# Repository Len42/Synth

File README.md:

# Synth

## Designs for my Eurorack synthesizer modules

This repo is where I am sharing my modular synthesizer designs.

[See here](https://lenp.net/synth/) for more info.

Please note that I am a hobbyist, not a trained electronics engineer! These designs are not perfect. The modules work for me, but I can't promise they'll work for everyone who builds them.

These designs are shared as open source. See the license details in each project and source file.

-- Len

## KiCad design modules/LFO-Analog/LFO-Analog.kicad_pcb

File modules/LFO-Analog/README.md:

# Dual Analog LFO

## 4HP Eurorack Module

### Features
- Two independent analog LFOs
- LFO rate from approximately 0.01 Hz (100 seconds) to 170 Hz, in two ranges
- Each LFO has sine and square wave outputs
- Not voltage controlled. Use your fingers! 👌

### Notes
(I have also made a [voltage-controlled digital LFO](https://github.com/Len42/Synth/tree/main/modules/LFO-DigiVC#readme).)

PCB layouts are provided in KiCad and gerber formats. A PCB layout for a drilled front panel (with no labels) is also included.

The PCBs that I used can be ordered from OSH Park. The designs are here:
- [Front panel](https://oshpark.com/shared_projects/gXxsPQ2r)
- [Controls board](https://oshpark.com/shared_projects/Vs8kgjxu)
- [Main board](https://oshpark.com/shared_projects/36ruR2I4)

There is a [parts list](bom.csv) in spreadsheet-friendly text format.

Please note that I am a hobbyist, not a trained electronics engineer. No guarantees!

### Software Used

* [KiCad](https://www.kicad.org/) 8.0.2

<hr /><div><div style="float:left; padding-right:10px;"></div><div style="xfloat:left; padding-left:10px;"><br />© 2024 Len Popp CC BY<br />This work is licensed under a <a rel="license" href="http://creativecommons.org/licenses/by/4.0/">Creative Commons Attribution 4.0 International License</a>.</div></div>

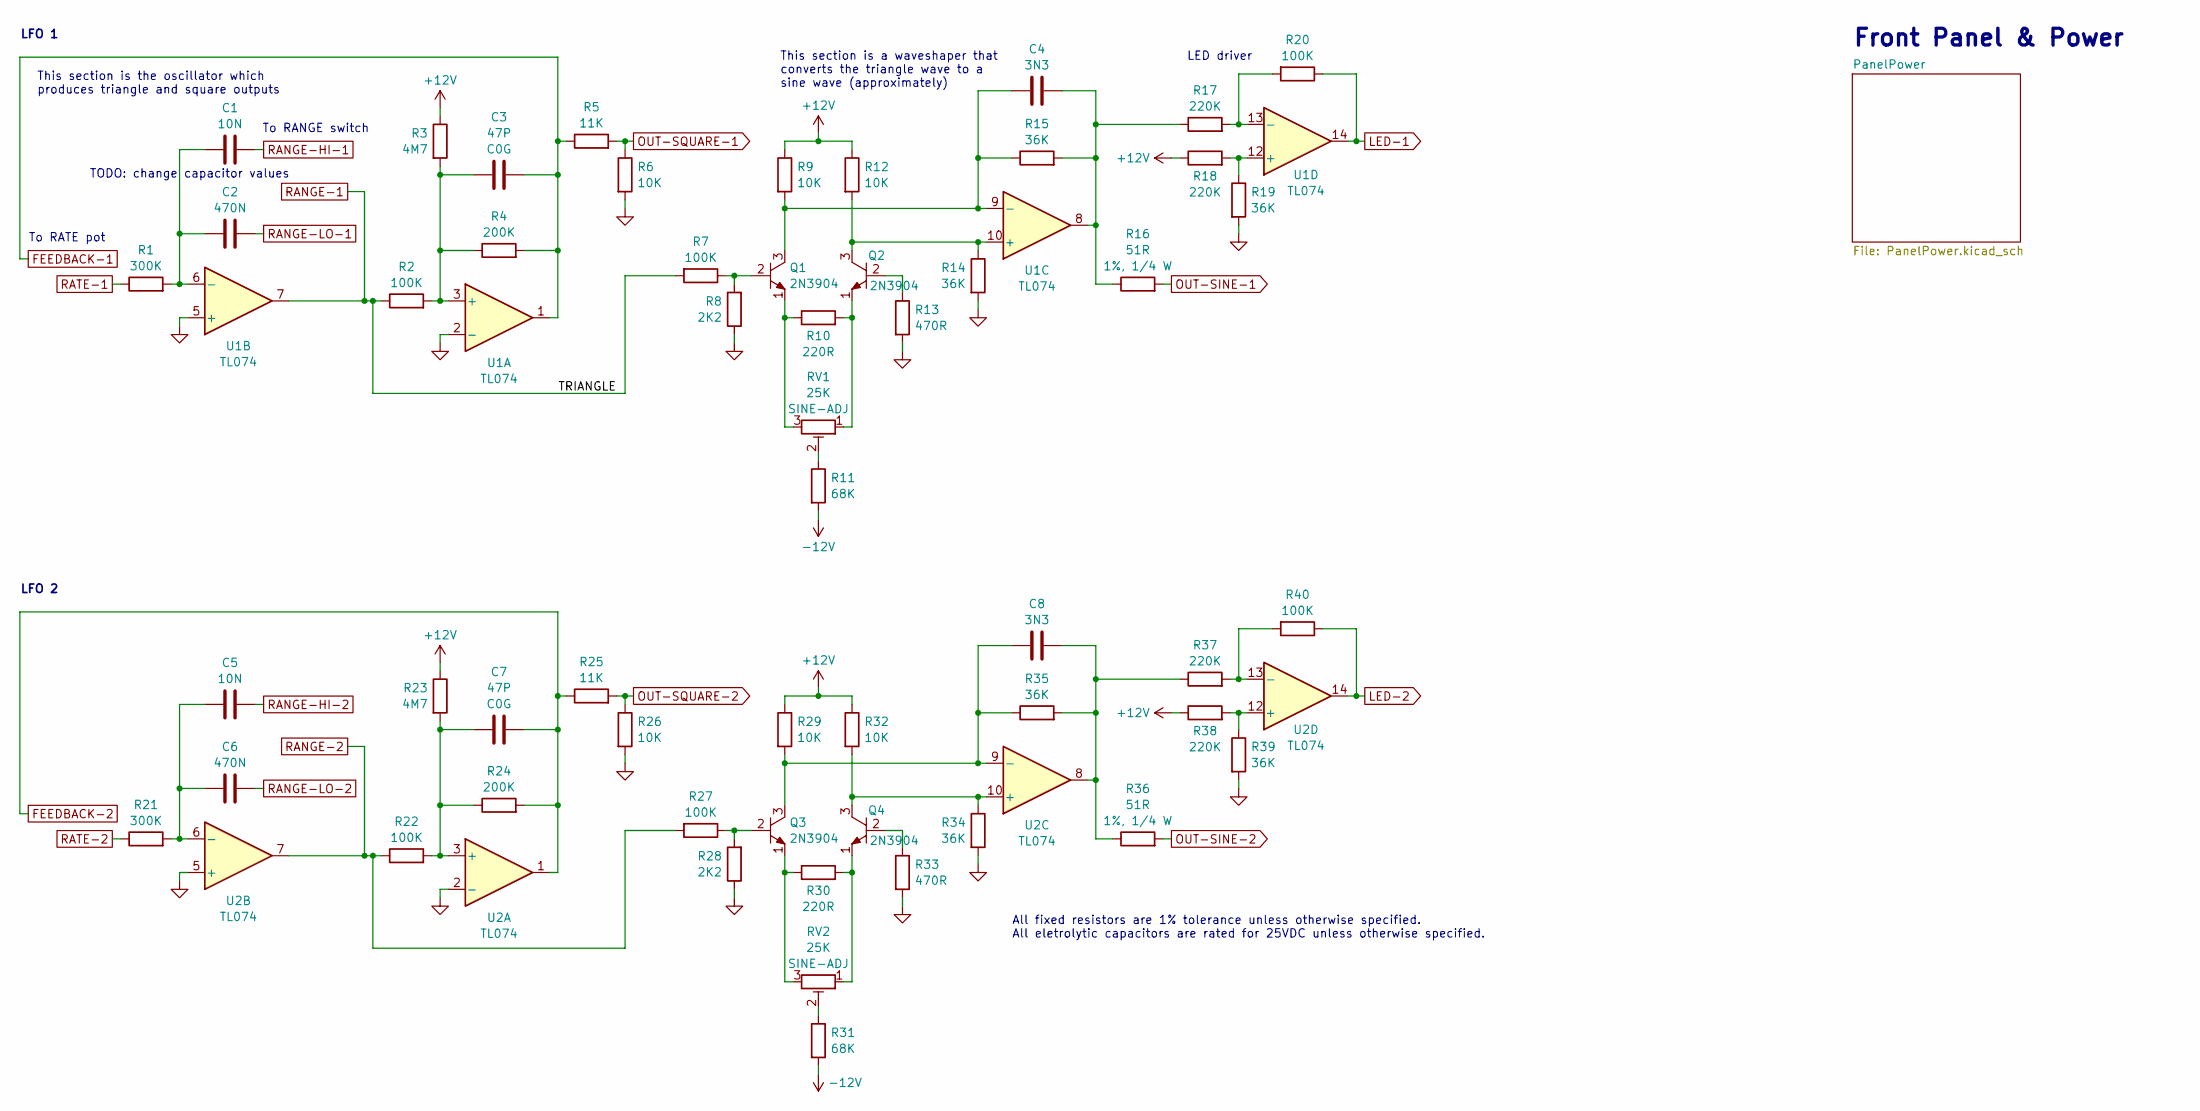
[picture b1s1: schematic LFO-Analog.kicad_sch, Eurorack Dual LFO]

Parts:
C1, C5: 10N; C_Rect_Kemet_L7.2mm_W2.5mm_P5mm; ManufacturerPartNum R82EC2100SH50J
C2, C6: 470N; C_Rect_L7.2mm_W4.5mm_P5.00mm; ManufacturerPartNum R82DC3470SH60J
C3, C7: 47P; C_Disc_D5.0mm_W2.5mm_P2.50mm; ManufacturerPartNum K470J15C0GF53L2
C4, C8: 3N3; C_Rect_Kemet_L7.2mm_W2.5mm_P5mm; ManufacturerPartNum R82EC1330AA50K
Q1, Q2, Q3, Q4: 2N3904; TO-92_Inline_Wide; ManufacturerPartNum 2N3904 PBFREE
R1, R21: 300K; R_Axial_DIN0207_L6.3mm_D2.5mm_P7.62mm_Horizontal; ManufacturerPartNum MFR-12FTF52-300K
R2, R7, R20, R22, R27, R40: 100K; R_Axial_DIN0207_L6.3mm_D2.5mm_P7.62mm_Horizontal; ManufacturerPartNum MFR-12FTF52-100K
R3, R23: 4M7; R_Axial_DIN0207_L6.3mm_D2.5mm_P7.62mm_Horizontal; ManufacturerPartNum MFR-12FTF52-4M7
R4, R24: 200K; R_Axial_DIN0207_L6.3mm_D2.5mm_P7.62mm_Horizontal; ManufacturerPartNum MFR-12FTF52-200K
R5, R25: 11K; R_Axial_DIN0207_L6.3mm_D2.5mm_P7.62mm_Horizontal; ManufacturerPartNum MFR-12FTF52-11K
R6, R9, R12, R26, R29, R32: 10K; R_Axial_DIN0207_L6.3mm_D2.5mm_P7.62mm_Horizontal; ManufacturerPartNum MFR-12FTF52-10K
R8, R28: 2K2; R_Axial_DIN0207_L6.3mm_D2.5mm_P7.62mm_Horizontal; ManufacturerPartNum MFR-12FTF52-2K2
R10, R30: 220R; R_Axial_DIN0207_L6.3mm_D2.5mm_P7.62mm_Horizontal; ManufacturerPartNum MFR-12FTF52-220R
R11, R31: 68K; R_Axial_DIN0207_L6.3mm_D2.5mm_P7.62mm_Horizontal; ManufacturerPartNum MFR-12FTF52-68K
R13, R33: 470R; R_Axial_DIN0207_L6.3mm_D2.5mm_P7.62mm_Horizontal; ManufacturerPartNum MFR-12FTF52-470R
R14, R15, R19, R34, R35, R39: 36K; R_Axial_DIN0207_L6.3mm_D2.5mm_P7.62mm_Horizontal; ManufacturerPartNum MFR-12FTF52-36K
R16, R36: 51R; R_Axial_DIN0207_L6.3mm_D2.5mm_P10.16mm_Horizontal; ManufacturerPartNum MFR-25FBF52-51R
R17, R18, R37, R38: 220K; R_Axial_DIN0207_L6.3mm_D2.5mm_P7.62mm_Horizontal; ManufacturerPartNum MFR-12FTF52-220K
RV1, RV2: 25K; Potentiometer_Bourns_3296W_Vertical; ManufacturerPartNum PV36W253C01B00
U1, U2: TL074; DIP-14_W7.62mm; ManufacturerPartNum TL074BCN

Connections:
+12V: R3.1, R9.1, R12.1, R18.1, R23.1, R29.1, R32.1, R38.1; also elsewhere on the board
-12V: R11.2, R31.2; also elsewhere on the board
FEEDBACK-1: C3.2, R4.2, R5.1, U1.1; also elsewhere on the board
FEEDBACK-2: C7.2, R24.2, R25.1, U2.1; also elsewhere on the board
GND: R6.2, R8.1, R13.2, R14.2, R19.2, R26.2, R28.1, R33.2, R34.2, R39.2, U1.2 (-), U1.5 (+), U2.2 (-), U2.5 (+); also elsewhere on the board
LED-1: R20.1, U1.14; also elsewhere on the board
LED-2: R40.1, U2.14; also elsewhere on the board
unnamed: C4.2, R15.2, R16.1, R17.1, U1.8
unnamed: C8.2, R35.2, R36.1, R37.1, U2.8
unnamed: Q1.2 (B), R7.1, R8.2
unnamed: C4.1, Q1.3 (C), R9.2, R15.1, U1.9 (-)
unnamed: Q1.1 (E), R10.1, RV1.3
unnamed: Q2.2 (B), R13.1
unnamed: Q2.3 (C), R12.2, R14.1, U1.10 (+)
unnamed: Q2.1 (E), R10.2, RV1.1
unnamed: Q3.2 (B), R27.1, R28.2
unnamed: C8.1, Q3.3 (C), R29.2, R35.1, U2.9 (-)
unnamed: Q3.1 (E), R30.1, RV2.3
unnamed: Q4.2 (B), R33.1
unnamed: Q4.3 (C), R32.2, R34.1, U2.10 (+)
unnamed: Q4.1 (E), R30.2, RV2.1
unnamed: R11.1, RV1.2
unnamed: R31.1, RV2.2
unnamed: C3.1, R2.2, R3.2, R4.1, U1.3 (+)
unnamed: C1.1, C2.1, R1.2, U1.6 (-)
unnamed: R18.2, R19.1, U1.12 (+)
unnamed: R17.2, R20.2, U1.13 (-)
unnamed: C7.1, R22.2, R23.2, R24.1, U2.3 (+)
unnamed: C5.1, C6.1, R21.2, U2.6 (-)
unnamed: R38.2, R39.1, U2.12 (+)
unnamed: R37.2, R40.2, U2.13 (-)
OUT-SINE-1: R16.2; also elsewhere on the board
OUT-SINE-2: R36.2; also elsewhere on the board
OUT-SQUARE-1: R5.2, R6.1; also elsewhere on the board
OUT-SQUARE-2: R25.2, R26.1; also elsewhere on the board
RANGE-1: R2.1, R7.2, U1.7; also elsewhere on the board
RANGE-2: R22.1, R27.2, U2.7; also elsewhere on the board
RANGE-HI-1: C1.2; also elsewhere on the board
RANGE-HI-2: C5.2; also elsewhere on the board
RANGE-LO-1: C2.2; also elsewhere on the board
RANGE-LO-2: C6.2; also elsewhere on the board
RATE-1: R1.1; also elsewhere on the board
RATE-2: R21.1; also elsewhere on the board

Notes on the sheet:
LFO 2
All fixed resistors are 1% tolerance unless otherwise specified. All eletrolytic capacitors are rated for 25VDC unless otherwise specified.
LED driver
TODO: change capacitor values
To RANGE switch
This section is the oscillator which produces triangle and square outputs
Front Panel & Power
LFO 1
This section is a waveshaper that converts the triangle wave to a sine wave (approximately)
To RATE pot

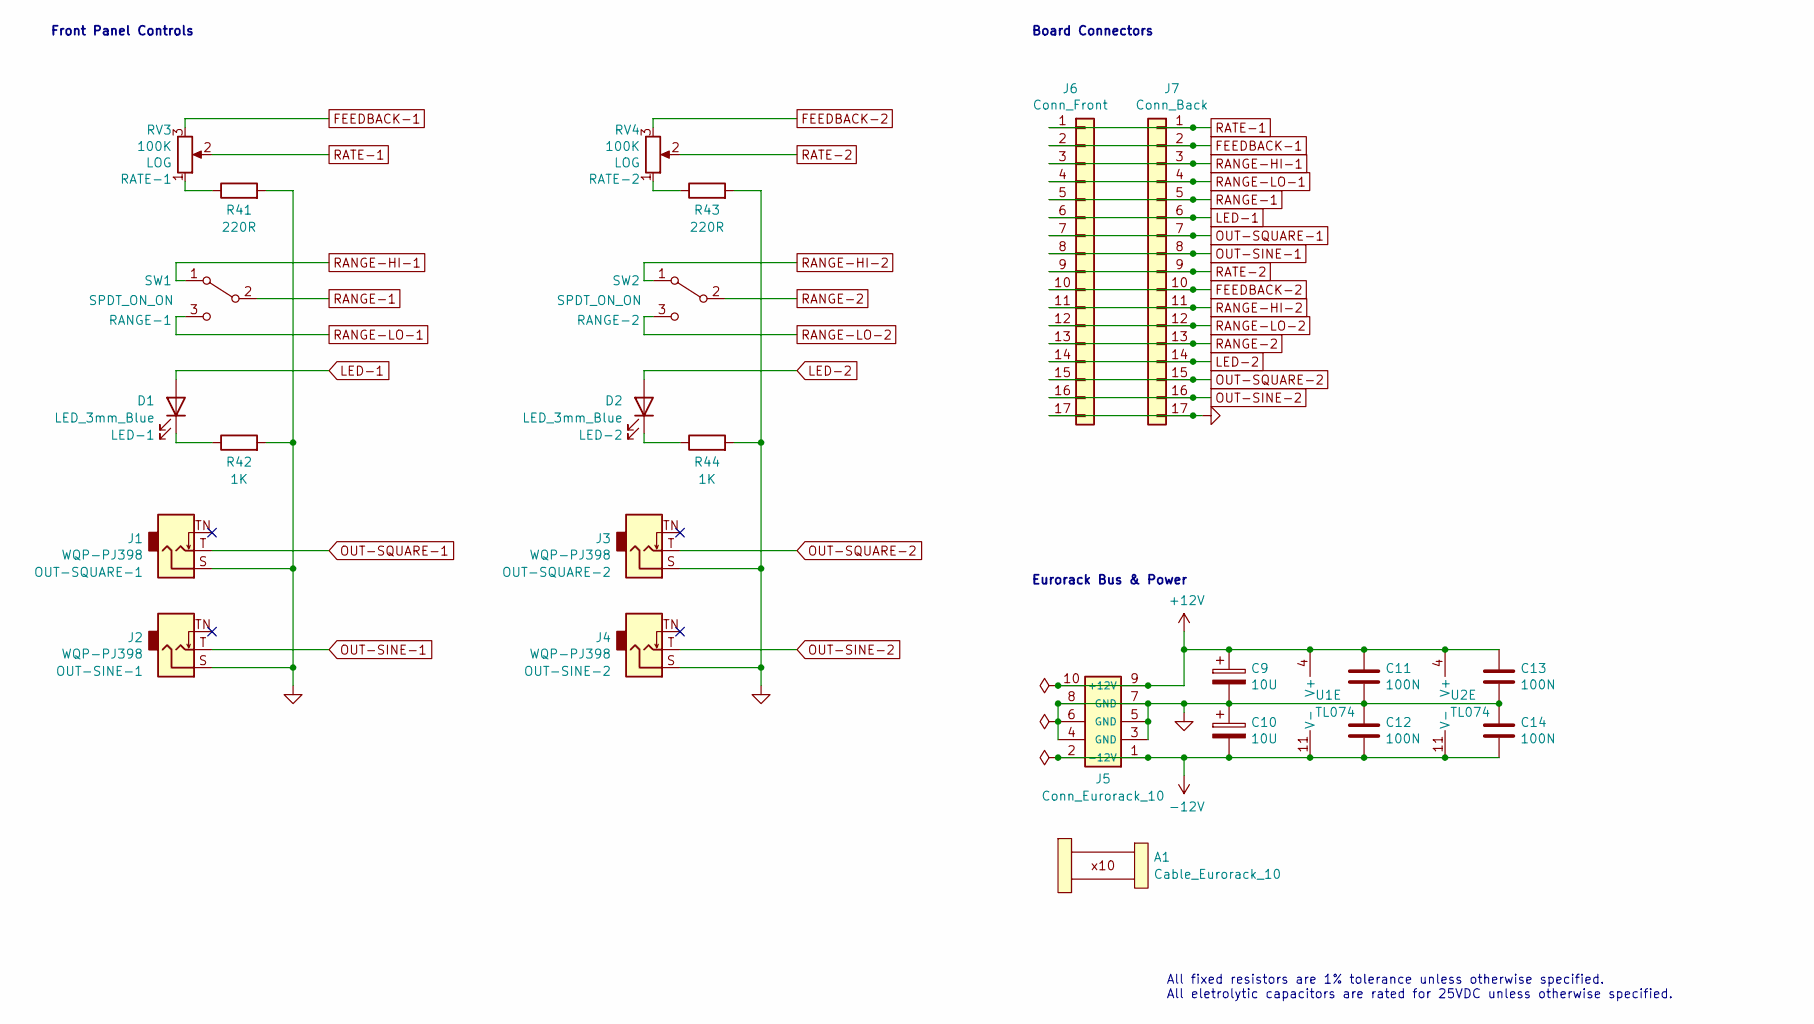
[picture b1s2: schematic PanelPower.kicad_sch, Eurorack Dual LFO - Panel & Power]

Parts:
A1: Cable_Eurorack_10; NoFootprint
C9, C10: 10U; CP_Radial_D5.0mm_P2.50mm; ManufacturerPartNum ECE-A1VKS100I
C11, C12, C13, C14: 100N; C_Disc_D5.0mm_W2.5mm_P2.50mm; ManufacturerPartNum FG18X7R1H104KNT06
D1, D2: LED_3mm_Blue; LED_D3.0mm_Clear; ManufacturerPartNum WP710A10QBD/D
J1, J2, J3, J4: WQP-PJ398; Jack_3.5mm_QingPu_WQP-PJ398SM_Vertical; ManufacturerPartNum PJ398SM / WQP518MA
J5: Conn_Eurorack_10; IDC-Header-Eurorack-10-TH; ManufacturerPartNum 61201021621
J6: Conn_Front; PinSocket_1x17_P2.54mm_Vertical
J7: Conn_Back; PinHeader_1x17_P2.54mm_Horizontal
R41, R43: 220R; R_Axial_DIN0207_L6.3mm_D2.5mm_P7.62mm_Horizontal; ManufacturerPartNum MFR-12FTF52-220R
R42, R44: 1K; R_Axial_DIN0207_L6.3mm_D2.5mm_P7.62mm_Horizontal; ManufacturerPartNum MFR-12FTF52-1K
RV3, RV4: 100K; Potentiometer_Alpha_RD901F-40-00D_Single_Vertical; ManufacturerPartNum RD901F-*
SW1, SW2: SPDT_ON_ON; SW_SPDT_THT_2.54; ManufacturerPartNum 10TC410
U1, U2: TL074; DIP-14_W7.62mm; ManufacturerPartNum TL074BCN

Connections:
+12V: C9.1, C11.1, C13.1, J5.9 (+12V), J5.10, U1.4 (V+), U2.4 (V+); also elsewhere on the board
-12V: C10.2, C12.2, C14.2, J5.1 (-12V), J5.2, U1.11 (V-), U2.11 (V-); also elsewhere on the board
FEEDBACK-1: J6.2, J7.2, RV3.3; also elsewhere on the board
FEEDBACK-2: J6.10, J7.10, RV4.3; also elsewhere on the board
GND: C9.2, C10.1, C11.2, C12.1, C13.2, C14.1, J1.S, J2.S, J3.S, J4.S, J5.3 (GND), J5.4, J5.5 (GND), J5.6, J5.7 (GND), J5.8, J6.17, J7.17, R41.2, R42.2, R43.2, R44.2; also elsewhere on the board
LED-1: D1.2 (A), J6.6, J7.6; also elsewhere on the board
LED-2: D2.2 (A), J6.14, J7.14; also elsewhere on the board
unnamed: D1.1 (K), R42.1
unnamed: D2.1 (K), R44.1
unnamed: R41.1, RV3.1
unnamed: R43.1, RV4.1
OUT-SINE-1: J2.T, J6.8, J7.8; also elsewhere on the board
OUT-SINE-2: J4.T, J6.16, J7.16; also elsewhere on the board
OUT-SQUARE-1: J1.T, J6.7, J7.7; also elsewhere on the board
OUT-SQUARE-2: J3.T, J6.15, J7.15; also elsewhere on the board
RANGE-1: J6.5, J7.5, SW1.2 (B); also elsewhere on the board
RANGE-2: J6.13, J7.13, SW2.2 (B); also elsewhere on the board
RANGE-HI-1: J6.3, J7.3, SW1.1 (A); also elsewhere on the board
RANGE-HI-2: J6.11, J7.11, SW2.1 (A); also elsewhere on the board
RANGE-LO-1: J6.4, J7.4, SW1.3 (C); also elsewhere on the board
RANGE-LO-2: J6.12, J7.12, SW2.3 (C); also elsewhere on the board
RATE-1: J6.1, J7.1, RV3.2; also elsewhere on the board
RATE-2: J6.9, J7.9, RV4.2; also elsewhere on the board

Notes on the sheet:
All fixed resistors are 1% tolerance unless otherwise specified. All eletrolytic capacitors are rated for 25VDC unless otherwise specified.
Eurorack Bus & Power
Board Connectors
Front Panel Controls

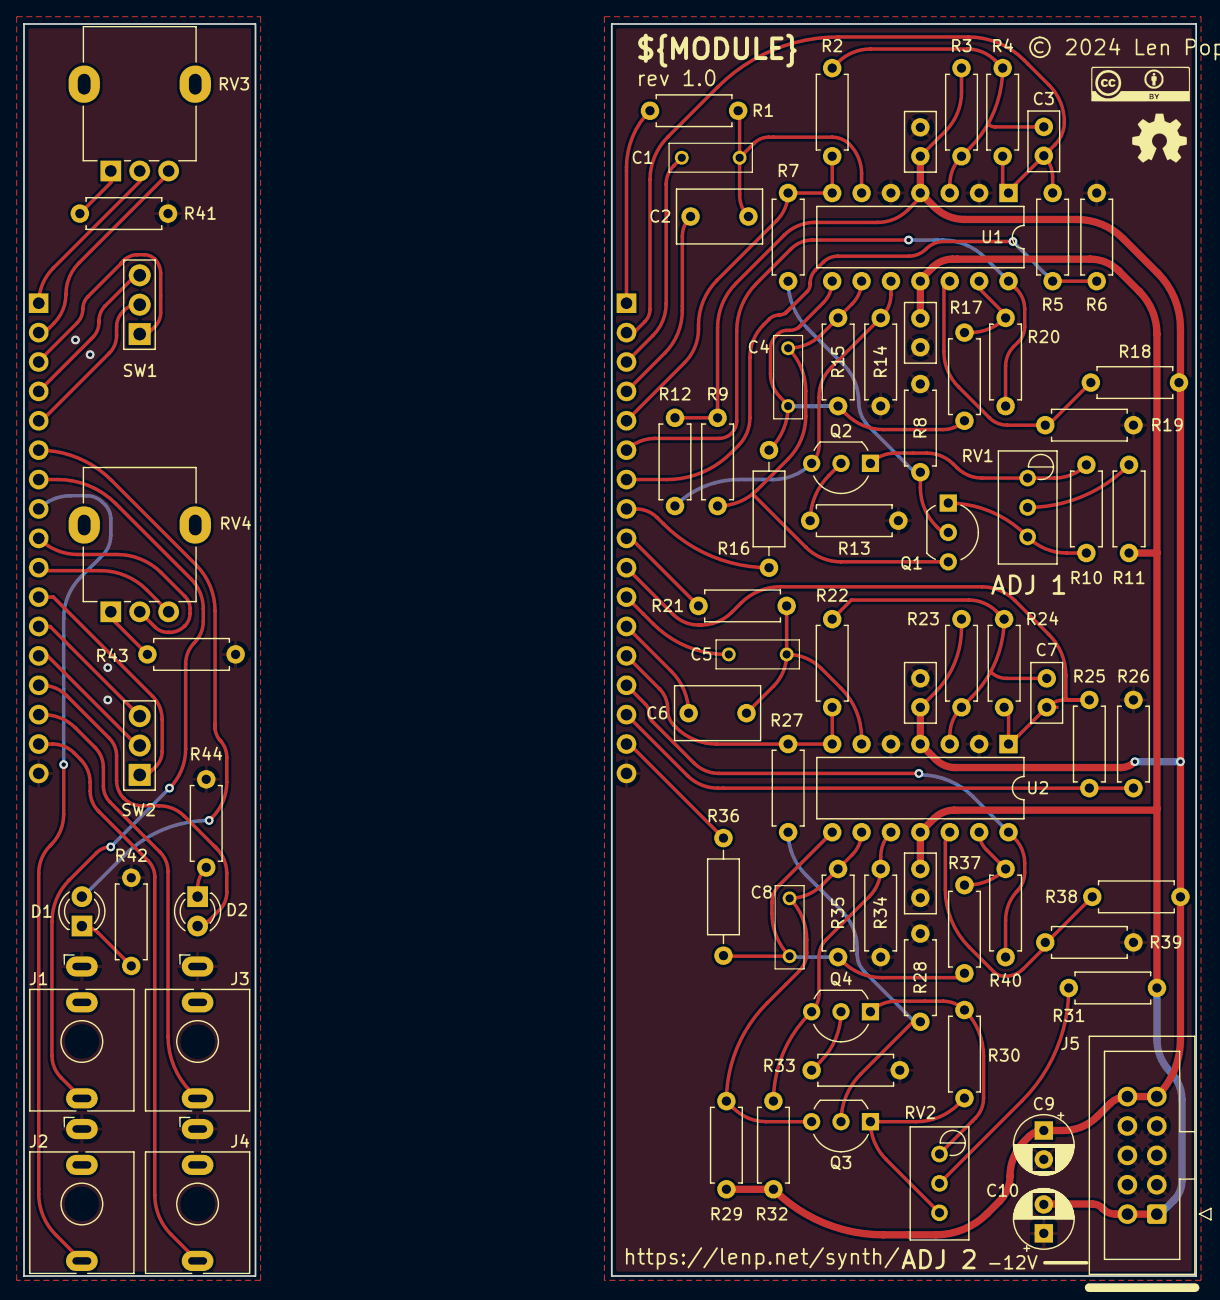
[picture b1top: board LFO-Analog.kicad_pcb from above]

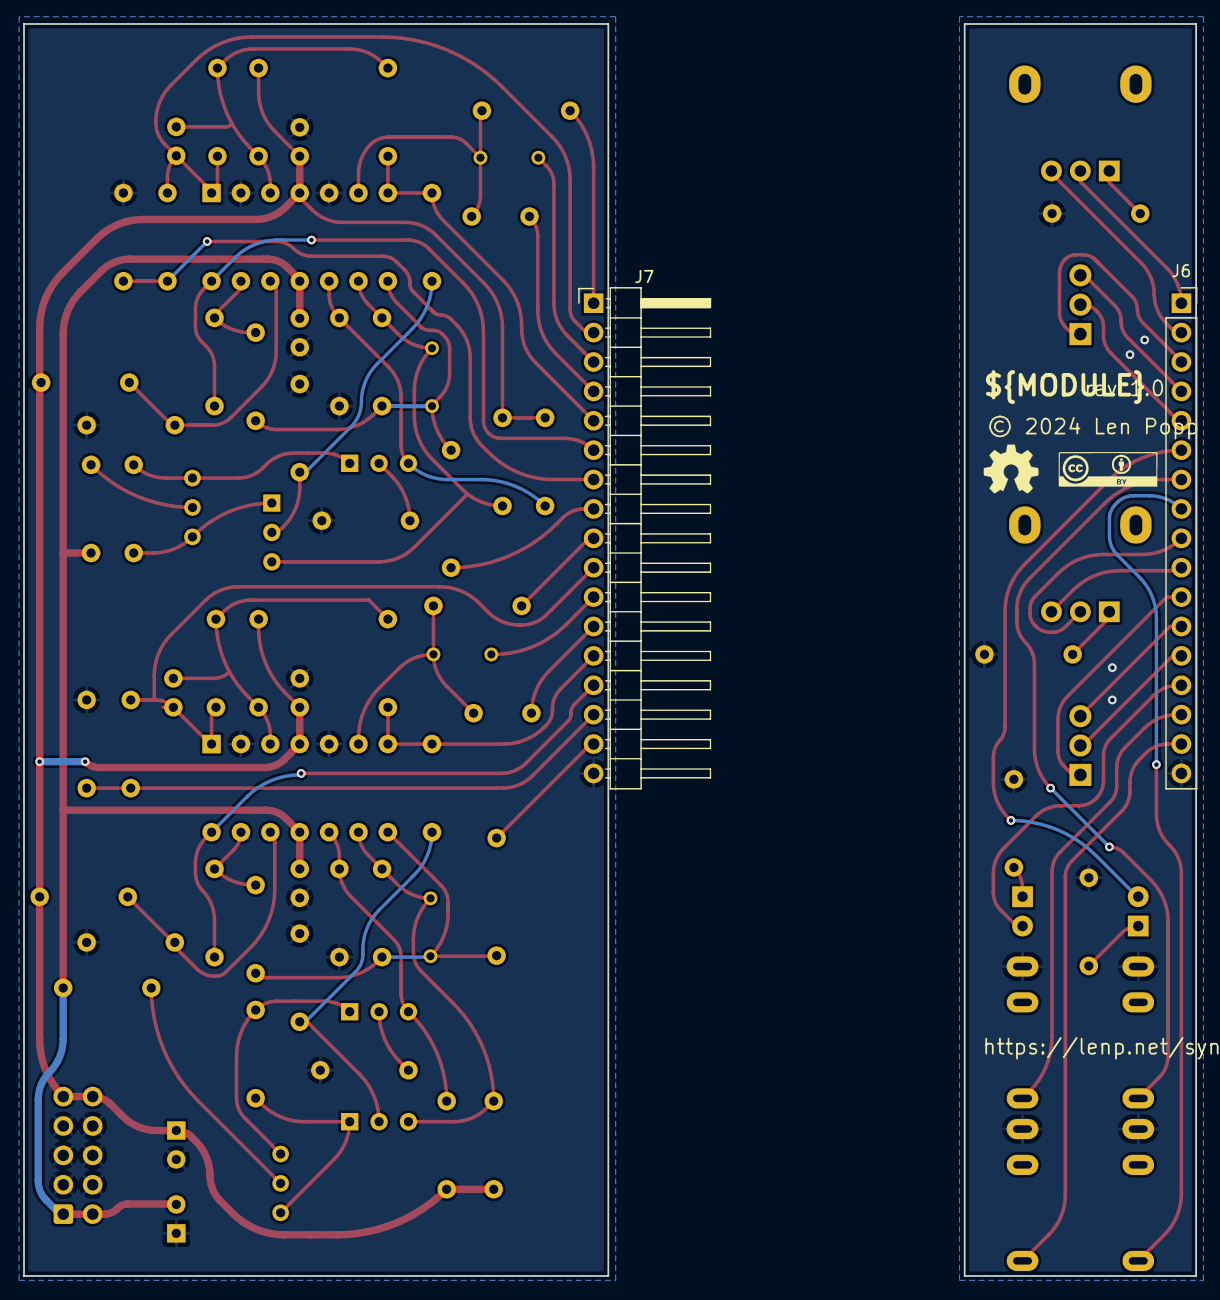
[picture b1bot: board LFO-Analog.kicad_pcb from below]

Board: 2 copper layers, 101.3 x 108.2 mm, 83 parts (4 on the bottom side), 47 nets.

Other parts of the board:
G1, G2: Logo_CC_BY
G3, G4: Logo_OSHW

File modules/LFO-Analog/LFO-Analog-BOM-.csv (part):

Ref,Qty,Value,Value2,Note,Description,Datasheet,Manufacturer,ManuPartNum,Distributor1,DistributorPartNum1,DistributorPartLink1,Distributor2,DistributorPartNum2,DistributorPartLink2,Distributor3,DistributorPartNum3,DistributorPartLink3
"A1","1","Cable_Eurorack_10","","Length as required","Eurorack 16-10 pin power cable","","","","Thonk","","https://www.thonk.co.uk/shop/eurorack-power-cables/","SynthCube","","https://synthcube.com/cart/eurorack-ribbon-power-cables","Modular Addict","","https://modularaddict.com/parts/eurorack-power-cables-1"
"C1 C5","2","3N3","","PPS for best results","Capacitor - Film","","","","","","","","","","","",""
"C2 C6","2","680N","","PPS for best results","Capacitor - Film","","","","","","","","","","","",""
"C3 C7","2","47P","C0G","","Capacitor - Ceramic","","","","","","","","","","","",""
"C4 C8","2","3N3","","","Capacitor - Film","","","","","","","","","","","",""
"C9 C10","2","10U","35 VDC","12 V decoupling","Capacitor - Electrolytic - 12 V decoupling","https://www.mouser.ca/datasheet/2/315/ABA0000C1059-947582.pdf","Panasonic","ECE-A1VKS100I","Mouser","667-ECE-A1VKS100I","https://www.mouser.ca/ProductDetail/667-ECE-A1VKS100I","Thonk","Group_Eurorack_DIY_Essential","https://www.thonk.co.uk/shop/eurorack-diy-essentials/","","",""
"C11 C12 C13 C14","4","100N","","IC decoupling","Capacitor - Ceramic - IC decoupling","https://product.tdk.com/system/files/dam/doc/product/capacit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","TDK","FG18X7R1H104KNT06","Mouser","810-FG18X7R1H104KNT6","https://www.mouser.ca/ProductDetail/810-FG18X7R1H104KNT6","","","","","",""
"D1 D2","2","LED_3mm_Blue","","","Blue Light Emitting Diode","https://www.mouser.ca/datasheet/2/239/Lite-On_LTL17KTBS3KS-0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","Kingbright","WP710A10QBD/D","Mouser","604-WP710A10QBD/D","https://www.mouser.ca/ProductDetail/Kingbright/WP710A10QBD-D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","","","","","",""
"J1 J2 J3 J4","4","WQP-PJ398","","","Audio Jack, 2 Poles (Mono / TS), Switched T Pole (Normalling), QingPu / Thonkiconn","http://www.qingpu-electronics.com/en/products/WQP-PJ398SM-362.html","QingPu / Thonk","PJ398SM / WQP518MA","Thonk","PJ398SM","https://www.thonk.co.uk/shop/thonkiconn/","SynthCube","WQP518MA","https://synthcube.com/cart/3-5mm-euro-jacks","Adafruit","4031","https://www.adafruit.com/product/4031"
"J5","1","Conn_Eurorack_10","","","Eurorack 10-pin board power connector","https://www.mouser.ca/datasheet/2/445/61201021621-1717731.pdf","Wurth Elektronik","61201021621","Mouser","710-61201021621","https://www.mouser.ca/ProductDetail/Wurth-Elektronik/6120102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","Thonk","","https://www.thonk.co.uk/shop/eurorack-diy-essentials/","","",""
"J6","1","Conn_Front","","","Generic connector, single row, 01x17, script generated (kicad-library-utils/schlib/autogen/connector/)","","","","Adafruit","598","https://www.adafruit.com/product/598","Mouser","710-61303211821","https://www.mouser.ca/ProductDetail/Wurth-Elektronik/6130321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","","",""
"J7","1","Conn_Back","","","Generic connector, single row, 01x17, script generated (kicad-library-utils/schlib/autogen/connector/)","","","","Adafruit","1540","https://www.adafruit.com/product/1540","Mouser","649-1012937993601BLF","https://www.mouser.ca/ProductDetail/Amphenol-FCI/10129379-93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","","",""
"Q1 Q2 Q3 Q4","4","2N3904","","","Small Signal NPN Transistor, 0.2A Ic, 40V Vce, TO-92","https://www.onsemi.com/pub/Collateral/2N3903-D.PDF","Central Semiconductor","2N3904 PBFREE","Mouser","610-2N3904","https://www.mouser.ca/ProductDetail/Central-Semiconductor/2N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","","","","","",""
"R1 R21","2","300K","1%, 1/6 W","","Resistor","https://www.mouser.ca/datasheet/2/447/YAGEO_MFR_datasheet_20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","YAGEO","MFR-12*","Mouser","603-MFR-12*","https://www.mouser.ca/c/?m=YAGEO&power+rating=166+mW+(1%2f6+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","","","","","",""
"R2 R7 R20 R22 R27 R40","6","100K","1%, 1/6 W","","Resistor","https://www.mouser.ca/datasheet/2/447/YAGEO_MFR_datasheet_20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","YAGEO","MFR-12*","Mouser","603-MFR-12*","https://www.mouser.ca/c/?m=YAGEO&power+rating=166+mW+(1%2f6+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","","","","","",""
"R3 R23","2","4M7","1%, 1/6 W","","Resistor","https://www.mouser.ca/datasheet/2/447/YAGEO_MFR_datasheet_20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","YAGEO","MFR-12*","Mouser","603-MFR-12*","https://www.mouser.ca/c/?m=YAGEO&power+rating=166+mW+(1%2f6+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","","","","","",""
"R4 R24","2","200K","1%, 1/6 W","","Resistor","https://www.mouser.ca/datasheet/2/447/YAGEO_MFR_datasheet_20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","YAGEO","MFR-12*","Mouser","603-MFR-12*","https://www.mouser.ca/c/?m=YAGEO&power+rating=166+mW+(1%2f6+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","","","","","",""
"R5 R25","2","11K","1%, 1/6 W","","Resistor","https://www.mouser.ca/datasheet/2/447/YAGEO_MFR_datasheet_20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","YAGEO","MFR-12*","Mouser","603-MFR-12*","https://www.mouser.ca/c/?m=YAGEO&power+rating=166+mW+(1%2f6+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","","","","","",""
"R6 R9 R12 R26 R29 R32","6","10K","1%, 1/6 W","","Resistor","https://www.mouser.ca/datasheet/2/447/YAGEO_MFR_datasheet_20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","YAGEO","MFR-12*","Mouser","603-MFR-12*","https://www.mouser.ca/c/?m=YAGEO&power+rating=166+mW+(1%2f6+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","","","","","",""
"R8 R28","2","2K2","1%, 1/6 W","","Resistor","https://www.mouser.ca/datasheet/2/447/YAGEO_MFR_datasheet_20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","YAGEO","MFR-12*","Mouser","603-MFR-12*","https://www.mouser.ca/c/?m=YAGEO&power+rating=166+mW+(1%2f6+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","","","","","",""
"R10 R30 R41 R43","4","220R","1%, 1/6 W","","Resistor","https://www.mouser.ca/datasheet/2/447/YAGEO_MFR_datasheet_20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","YAGEO","MFR-12*","Mouser","603-MFR-12*","https://www.mouser.ca/c/?m=YAGEO&power+rating=166+mW+(1%2f6+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","","","","","",""
"R11 R31","2","68K","1%, 1/6 W","","Resistor","https://www.mouser.ca/datasheet/2/447/YAGEO_MFR_datasheet_20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","YAGEO","MFR-12*","Mouser","603-MFR-12*","https://www.mouser.ca/c/?m=YAGEO&power+rating=166+mW+(1%2f6+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","","","","","",""
"R13 R33","2","470R","1%, 1/6 W","","Resistor","https://www.mouser.ca/datasheet/2/447/YAGEO_MFR_datasheet_20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","YAGEO","MFR-12*","Mouser","603-MFR-12*","https://www.mouser.ca/c/?m=YAGEO&power+rating=166+mW+(1%2f6+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","","","","","",""
"R14 R15 R19 R34 R35 R39","6","36K","1%, 1/6 W","","Resistor","https://www.mouser.ca/datasheet/2/447/YAGEO_MFR_datasheet_20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","YAGEO","MFR-12*","Mouser","603-MFR-12*","https://www.mouser.ca/c/?m=YAGEO&power+rating=166+mW+(1%2f6+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","","","","","",""
"R16 R36","2","51R","1%, 1/4 W","Output limiting","Resistor","https://www.mouser.ca/datasheet/2/447/Yageo_LR_MFR_1-1714151.pdf","YAGEO","MFR-25FBF52-51R","Mouser","603-MFR-25FBF52-51R","https://www.mouser.ca/ProductDetail/?qs=oAGoVhmvjhzVx2bdEH1T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","","","","","",""
"R17 R18 R37 R38","4","220K","1%, 1/6 W","","Resistor","https://www.mouser.ca/datasheet/2/447/YAGEO_MFR_datasheet_20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","YAGEO","MFR-12*","Mouser","603-MFR-12*","https://www.mouser.ca/c/?m=YAGEO&power+rating=166+mW+(1%2f6+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","","","","","",""
"R42 R44","2","1K","1%, 1/6 W","","Resistor","https://www.mouser.ca/datasheet/2/447/YAGEO_MFR_datasheet_20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","YAGEO","MFR-12*","Mouser","603-MFR-12*","https://www.mouser.ca/c/?m=YAGEO&power+rating=166+mW+(1%2f6+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","","","","","",""
"RV1 RV2","2","25K","","","Trim-potentiometer","https://www.mouser.ca/datasheet/2/54/3296-776415.pdf","Bourns","3296X-*","Mouser","652-3296Z-*","https://www.mouser.ca/c/passive-components/potentiometers-tr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","","","","","",""
"RV3 RV4","2","100K","LOG","","Potentiometer","https://www.mouser.ca/datasheet/2/13/alpha_taiwan_08192019_R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","Alpha","RD901F-*","Thonk","Group_Pot_Alpha_6.35mm","https://www.thonk.co.uk/shop/alpha-9mm-pots/","Mouser","311-1940F-*","https://www.mouser.ca/c/passive-components/potentiometers-tr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","SynthCube","9MMALPHAPOTMSTR","https://synthcube.com/cart/alpha-9mm-potentiometer-right-ang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"
"SW1 SW2","2","SPDT_ON_ON","","","Switch, single pole double throw sub-mini toggle","https://www.mouser.ca/datasheet/2/221/MS-100542-1173960.pdf","Mountain Switch","10TC410","Mouser","10TC410","https://www.mouser.ca/ProductDetail/Mountain-Switch/10TC410?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","Thonk","","https://www.thonk.co.uk/shop/sub-mini-toggle-switches/","SynthCube","","https://synthcube.com/cart/toggle-switch-submini-pc-pin"
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
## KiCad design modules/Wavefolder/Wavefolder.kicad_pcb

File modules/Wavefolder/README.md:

# Simple Wavefolder V2

## 4HP Eurorack Module

### Features
- Two separate wavefolding channels
- Channel 1 output is normalled to channel 2 input to give double the folding
- Front panel knobs control the degree of folding for each channel

### Notes
This is version 2 of the Wavefolder module. [Version 1](../Wavefolder-v1/) used the same circuit but was built using the [Delptronics Module Construction Set](https://delptronics.com/module-construction-set.php) instead of a custom PCB.

The amount of folding is controlled by the level of the input signal which is adjusted by an attenuator pot on the input. There are no CV inputs, but CV control of the folding can be done by running the input signal through a VCA.

The circuit design is based on [Ken Stone's Simple Wave Folder](https://www.elby-designs.com/webtek/cgs/cgs52/cgs52_folder.html) and [yusynth's Metalizer](http://yusynth.net/Modular/EN/METALIZER/).

PCB layouts are provided in KiCad and gerber formats. A PCB layout for a drilled front panel (with no labels) is also included.

The PCBs that I used can be ordered from OSH Park. The designs are here:
- [Front panel](https://oshpark.com/shared_projects/uywe7ayj)
- [Controls board](https://oshpark.com/shared_projects/bExOOKeW)
- [Main board](https://oshpark.com/shared_projects/pl6nXBNP)

Please note that I am a hobbyist, not a trained electronics engineer. No guarantees!

### Software Used

* [KiCad](https://www.kicad.org/) 7.0.8

<hr /><div><div style="float:left; padding-right:10px;"></div><div style="padding-left:10px;"><br />© 2024 Len Popp CC BY<br />This work is licensed under a <a rel="license" href="http://creativecommons.org/licenses/by/4.0/">Creative Commons Attribution 4.0 International License</a>.</div></div>

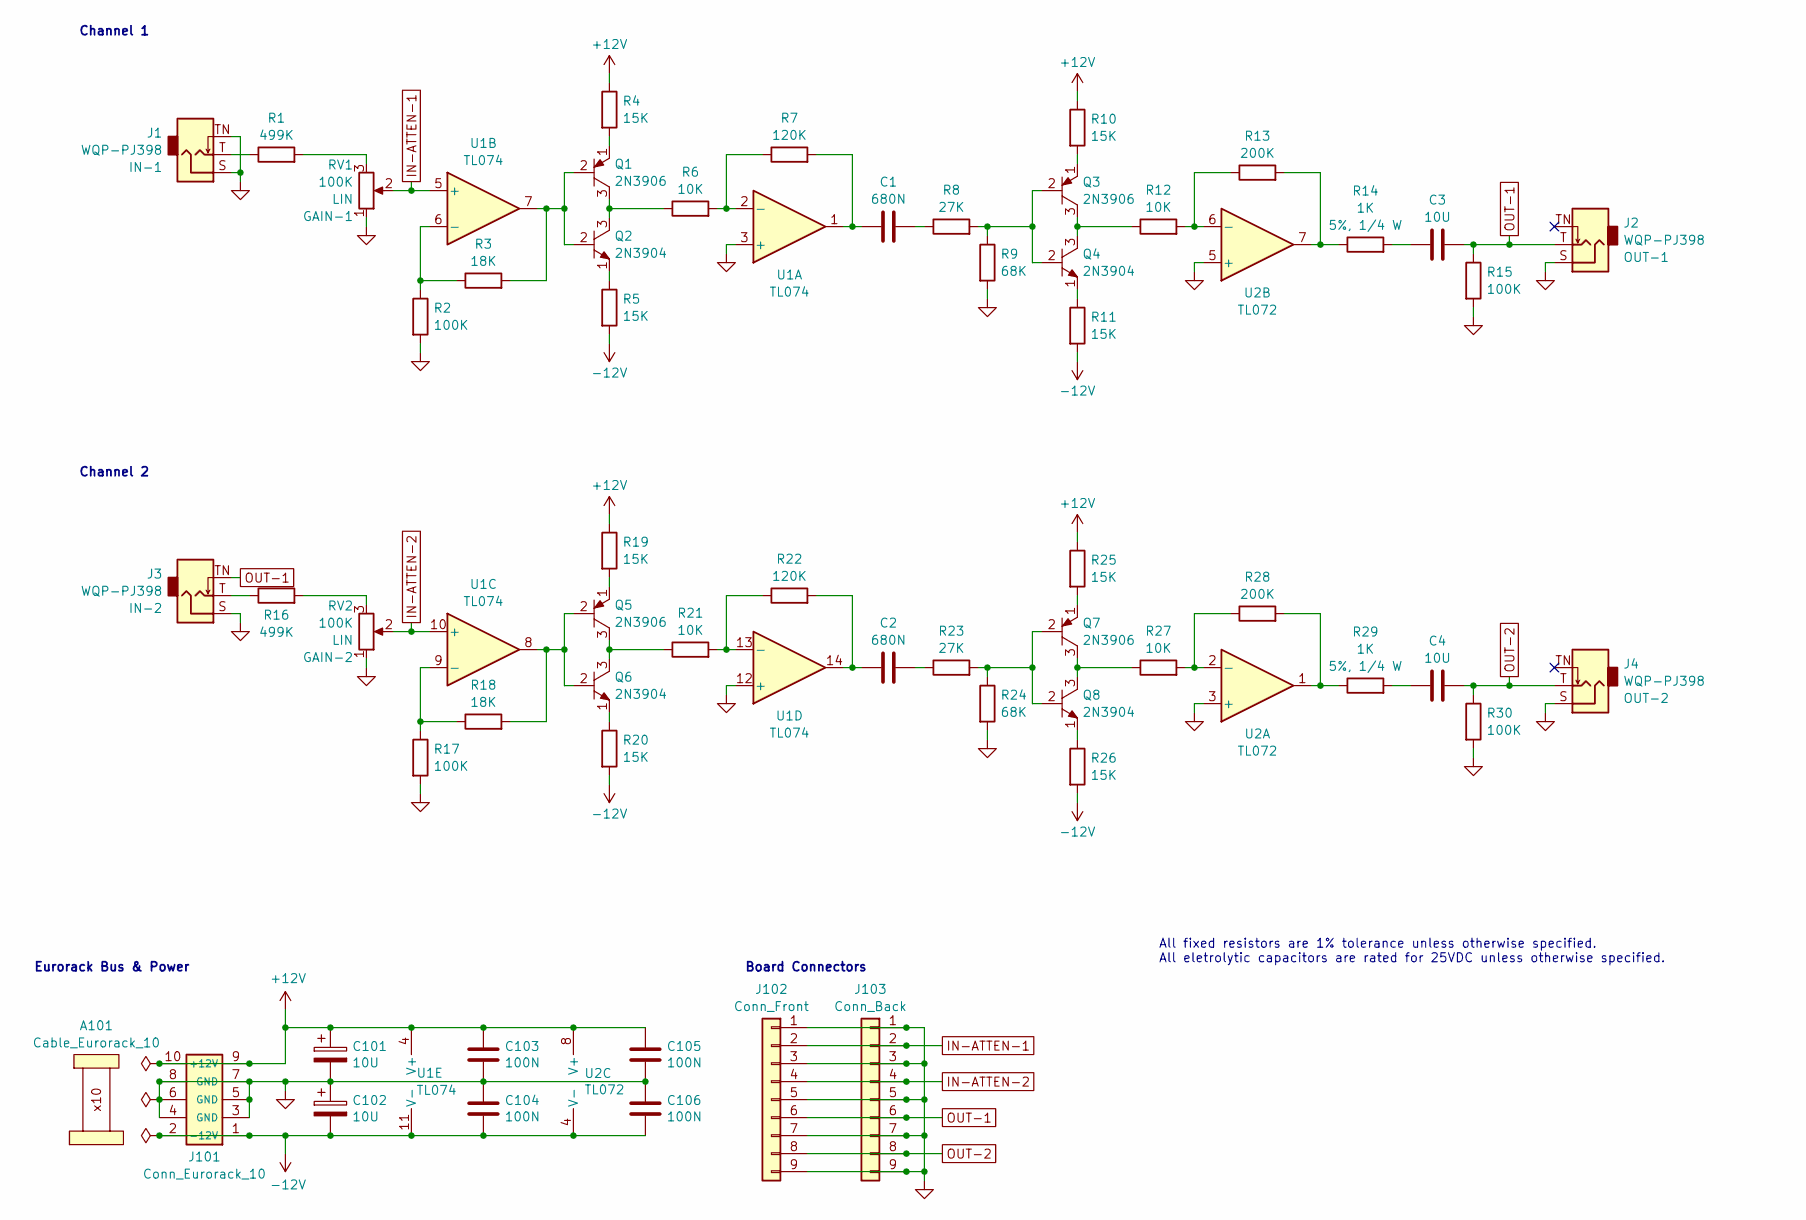
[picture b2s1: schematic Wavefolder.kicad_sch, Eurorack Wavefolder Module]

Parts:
A101: Cable_Eurorack_10; NoFootprint
C1, C2: 680N; C_Rect_L7.2mm_W4.5mm_P5.00mm; ManufacturerPartNum R82DC3680AA60K
C3, C4: 10U; C_Radial_D5.0mm_H5.0mm_P2.50mm; ManufacturerPartNum ECE-A1EN100UI
C101, C102: 10U; CP_Radial_D5.0mm_P2.50mm; ManufacturerPartNum ECE-A1VKS100I
C103, C104, C105, C106: 100N; C_Disc_D5.0mm_W2.5mm_P2.50mm; ManufacturerPartNum FG18X7R1H104KNT06
J1, J2, J3, J4: WQP-PJ398; Jack_3.5mm_QingPu_WQP-PJ398SM_Vertical; ManufacturerPartNum PJ398SM / WQP518MA
J101: Conn_Eurorack_10; IDC-Header-Eurorack-10-TH; ManufacturerPartNum 61201021621
J102: Conn_Front; PinSocket_1x09_P2.54mm_Vertical
J103: Conn_Back; PinHeader_1x09_P2.54mm_Horizontal
Q1, Q3, Q5, Q7: 2N3906; TO-92_Inline_Wide; ManufacturerPartNum 2N3906TAR
Q2, Q4, Q6, Q8: 2N3904; TO-92_Inline_Wide; ManufacturerPartNum 2N3904 PBFREE
R1, R16: 499K; R_Axial_DIN0207_L6.3mm_D2.5mm_P7.62mm_Horizontal; ManufacturerPartNum MFR-25FTE52-499K
R2, R15, R17, R30: 100K; R_Axial_DIN0207_L6.3mm_D2.5mm_P7.62mm_Horizontal; ManufacturerPartNum MFR-12FTF52-100K
R3, R18: 18K; R_Axial_DIN0207_L6.3mm_D2.5mm_P7.62mm_Horizontal; ManufacturerPartNum MFR-12FTF52-18K
R4, R5, R10, R11, R19, R25, R26: 15K; R_Axial_DIN0207_L6.3mm_D2.5mm_P7.62mm_Horizontal; ManufacturerPartNum MFR-12FTF52-15K
R6, R12, R21, R27: 10K; R_Axial_DIN0207_L6.3mm_D2.5mm_P7.62mm_Horizontal; ManufacturerPartNum MFR-12FTF52-10K
R7, R22: 120K; R_Axial_DIN0207_L6.3mm_D2.5mm_P7.62mm_Horizontal; ManufacturerPartNum MFR-12FTF52-120K
R8, R23: 27K; R_Axial_DIN0207_L6.3mm_D2.5mm_P7.62mm_Horizontal; ManufacturerPartNum MFR-12FTF52-27K
R9, R24: 68K; R_Axial_DIN0207_L6.3mm_D2.5mm_P7.62mm_Horizontal; ManufacturerPartNum MFR-12FTF52-68K
R13, R28: 200K; R_Axial_DIN0207_L6.3mm_D2.5mm_P7.62mm_Horizontal; ManufacturerPartNum MFR-12FTF52-200K
R14, R29: 1K; R_Axial_DIN0207_L6.3mm_D2.5mm_P10.16mm_Horizontal; ManufacturerPartNum CCF071K00JKE36
R20: 15K; SB_Gen_1; ManufacturerPartNum MFR-12FTF52-15K
RV1, RV2: 100K; Potentiometer_Alpha_RD901F-40-00D_Single_Vertical; ManufacturerPartNum RD901F-*
U1: TL074; DIP-14_W7.62mm; ManufacturerPartNum TL074BCN
U2: TL072; DIP-8_W7.62mm; ManufacturerPartNum TL072BCP

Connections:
+12V: C101.1, C103.1, C105.1, J101.9 (+12V), J101.10, R4.1, R10.1, R19.1, R25.1, U1.4 (V+), U2.8 (V+)
-12V: C102.2, C104.2, C106.2, J101.1 (-12V), J101.2, R5.2, R11.2, R20.2, R26.2, U1.11 (V-), U2.4 (V-)
GND: C101.2, C102.1, C103.2, C104.1, C105.2, C106.1, J1.S, J1.TN, J2.S, J3.S, J4.S, J101.3 (GND), J101.4, J101.5 (GND), J101.6, J101.7 (GND), J101.8, J102.1, J102.3, J102.5, J102.7, J102.9, J103.1, J103.3, J103.5, J103.7, J103.9, R2.2, R9.2, R15.2, R17.2, R24.2, R30.2, RV1.1, RV2.1, U1.3 (+), U1.12 (+), U2.3 (+), U2.5 (+)
IN-ATTEN-1: J102.2, J103.2, RV1.2, U1.5 (+)
IN-ATTEN-2: J102.4, J103.4, RV2.2, U1.10 (+)
unnamed: C1.1, R7.2, U1.1
unnamed: C1.2, R8.1
unnamed: C2.1, R22.2, U1.14
unnamed: C2.2, R23.1
unnamed: C3.1, R14.2
unnamed: C4.1, R29.2
unnamed: J1.T, R1.1
unnamed: J3.T, R16.1
unnamed: Q1.2 (B), Q2.2 (B), R3.2, U1.7
unnamed: Q1.3 (C), Q2.3 (C), R6.1
unnamed: Q1.1 (E), R4.2
unnamed: Q2.1 (E), R5.1
unnamed: Q3.2 (B), Q4.2 (B), R8.2, R9.1
unnamed: Q3.3 (C), Q4.3 (C), R12.1
unnamed: Q3.1 (E), R10.2
unnamed: Q4.1 (E), R11.1
unnamed: Q5.2 (B), Q6.2 (B), R18.2, U1.8
unnamed: Q5.3 (C), Q6.3 (C), R21.1
unnamed: Q5.1 (E), R19.2
unnamed: Q6.1 (E), R20.1
unnamed: Q7.2 (B), Q8.2 (B), R23.2, R24.1
unnamed: Q7.3 (C), Q8.3 (C), R27.1
unnamed: Q7.1 (E), R25.2
unnamed: Q8.1 (E), R26.1
unnamed: R1.2, RV1.3
unnamed: R13.2, R14.1, U2.7
unnamed: R16.2, RV2.3
unnamed: R28.2, R29.1, U2.1
unnamed: R6.2, R7.1, U1.2 (-)
unnamed: R2.1, R3.1, U1.6 (-)
unnamed: R17.1, R18.1, U1.9 (-)
unnamed: R21.2, R22.1, U1.13 (-)
unnamed: R27.2, R28.1, U2.2 (-)
unnamed: R12.2, R13.1, U2.6 (-)
OUT-1: C3.2, J2.T, J3.TN, J102.6, J103.6, R15.1
OUT-2: C4.2, J4.T, J102.8, J103.8, R30.1

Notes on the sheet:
All fixed resistors are 1% tolerance unless otherwise specified. All eletrolytic capacitors are rated for 25VDC unless otherwise specified.
Eurorack Bus & Power
Board Connectors
Channel 2
Channel 1

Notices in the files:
misc/Attenuator/Attenuator.kicad_pcb:
Copyright © 2024 Len Popp CC BY
modules/Adder/PanelPower.kicad_sch:
Copyright © 2022 Len Popp CC BY
modules/Filter2/Filter2.kicad_pcb:
Copyright © 2023 Len Popp CC BY
modules/Wavefolder-v1/Wavefolder.kicad_sch:
Copyright © 2021 Len Popp CC BY
